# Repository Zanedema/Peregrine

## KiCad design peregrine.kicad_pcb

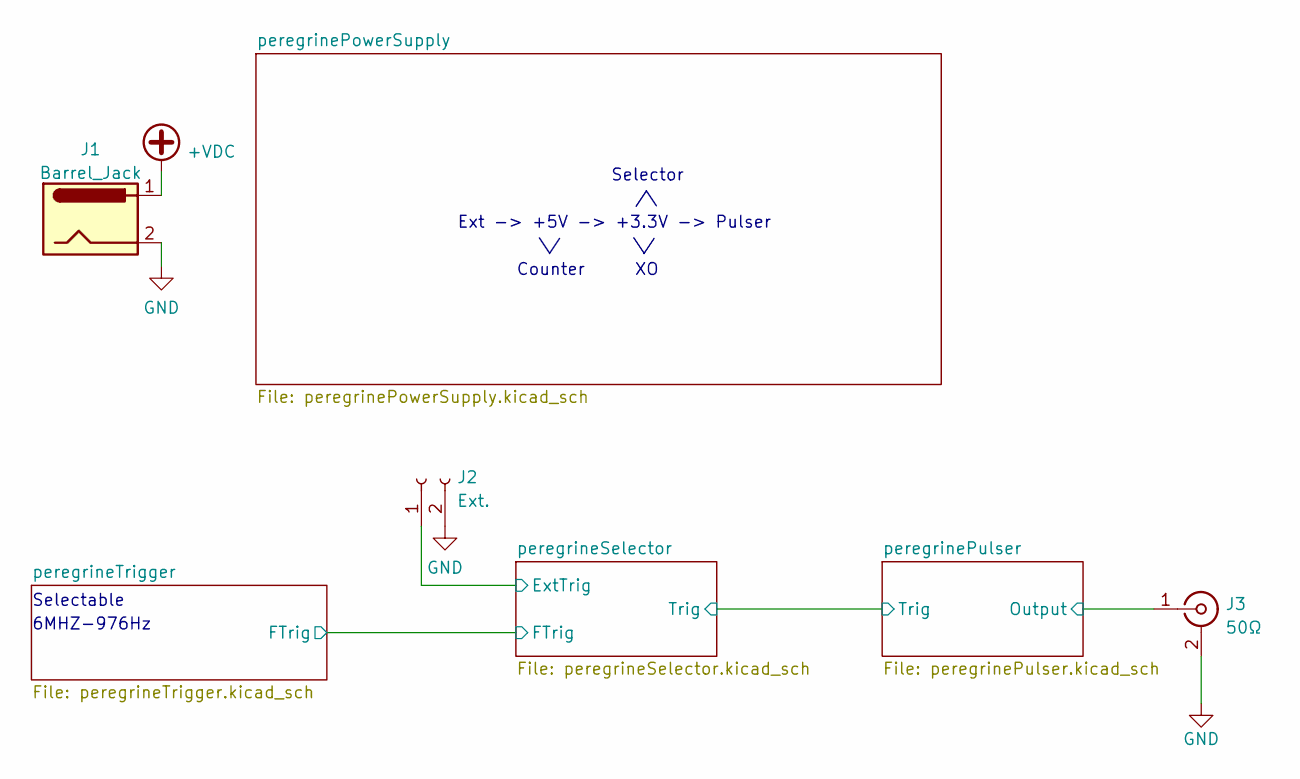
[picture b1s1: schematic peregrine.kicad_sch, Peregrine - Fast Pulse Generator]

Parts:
J1: Barrel_Jack; KLDX-0202-A
J2: Ext.; PinHeader_1x02_P2.54mm_Vertical
J3: 50Ω; LINX_CONSMA020.062-G

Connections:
+VDC: J1.1; also elsewhere on the board
/peregrinePulser/Output: J3.1 (In); also elsewhere on the board
/peregrineSelector/ExtTrig: J2.1; also elsewhere on the board
GND: J1.2, J2.2, J3.2 (Ext); also elsewhere on the board

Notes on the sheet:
Ext -> +5V -> +3.3V -> Pulser
Selectable
6MHZ-976Hz
Counter
Selector

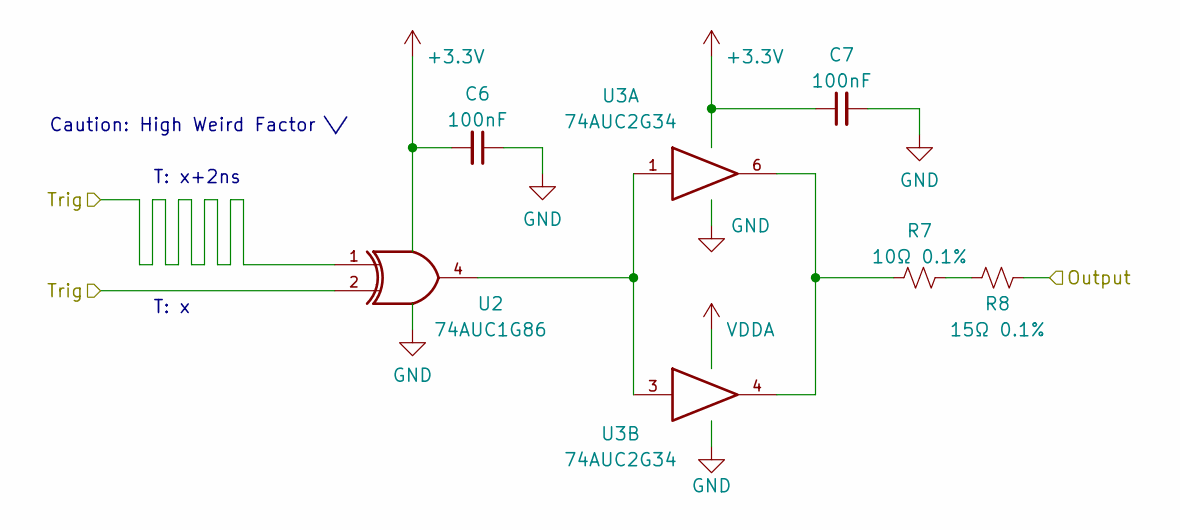
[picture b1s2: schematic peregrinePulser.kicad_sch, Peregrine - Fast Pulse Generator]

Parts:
C6, C7: 100nF; C_0603_1608Metric_Pad1.08x0.95mm_HandSolder
R7: 10Ω 0.1%; R_0603_1608Metric_Pad0.98x0.95mm_HandSolder
R8: 15Ω 0.1%; R_0603_1608Metric_Pad0.98x0.95mm_HandSolder
U2: 74AUC1G86; SOT-353_SC-70-5_Handsoldering
U3: 74AUC2G34; SOT-363_SC-70-6_Handsoldering

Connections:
/peregrinePulser/Output: R8.1; also elsewhere on the board
/peregrinePulser/Trig: U2.1, U2.2; also elsewhere on the board
GND: C6.1, C7.2, U2.3 (GND), U3.2 (GND); also elsewhere on the board
unnamed: R7.1, R8.2
unnamed: R7.2, U3.4, U3.6
unnamed: U2.4, U3.1, U3.3

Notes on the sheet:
T: x+2ns
Caution: High Weird Factor \/
T: x

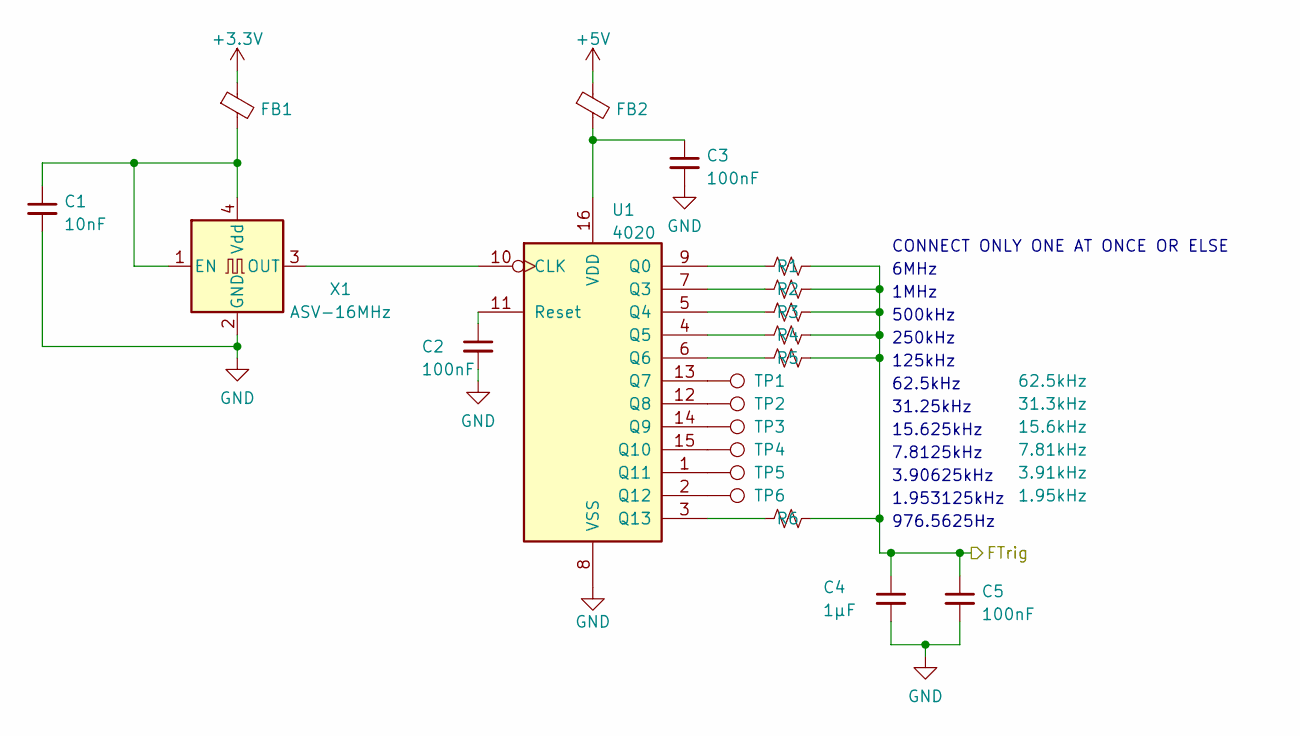
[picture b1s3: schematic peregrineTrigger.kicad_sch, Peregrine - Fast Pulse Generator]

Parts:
C1: 10nF; C_0603_1608Metric_Pad1.08x0.95mm_HandSolder
C2, C3, C5: 100nF; C_0603_1608Metric_Pad1.08x0.95mm_HandSolder
C4: 1μF; C_0603_1608Metric_Pad1.08x0.95mm_HandSolder
FB1, FB2: FerriteBead_Small; L_0603_1608Metric_Pad1.05x0.95mm_HandSolder
R1, R2, R3, R4, R5, R6: 0; R_0402_1005Metric_Pad0.72x0.64mm_HandSolder
TP1: 62.5kHz; TestPoint_Pad_D1.0mm
TP2: 31.3kHz; TestPoint_Pad_D1.0mm
TP3: 15.6kHz; TestPoint_Pad_D1.0mm
TP4: 7.81kHz; TestPoint_Pad_D1.0mm
TP5: 3.91kHz; TestPoint_Pad_D1.0mm
TP6: 1.95kHz; TestPoint_Pad_D1.0mm
U1: 4020; TSSOP-16_4.4x5mm_P0.65mm
X1: ASV-16MHz; Oscillator_SMD_Abracon_ASV-4Pin_7.0x5.1mm

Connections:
+5V: FB2.1; also elsewhere on the board
/peregrineSelector/FTrig: C4.1, C5.1, R1.1, R2.1, R3.1, R4.1, R5.1, R6.1; also elsewhere on the board
GND: C1.2, C2.2, C3.2, C4.2, C5.2, U1.8 (VSS), X1.2 (GND); also elsewhere on the board
unnamed: C1.1, FB1.2, X1.1 (EN), X1.4 (Vdd)
unnamed: C2.1, U1.11 (Reset)
unnamed: C3.1, FB2.2, U1.16 (VDD)
unnamed: R1.2, U1.9 (Q0)
unnamed: R2.2, U1.7 (Q3)
unnamed: R3.2, U1.5 (Q4)
unnamed: R4.2, U1.4 (Q5)
unnamed: R5.2, U1.6 (Q6)
unnamed: R6.2, U1.3 (Q13)
unnamed: TP1.1, U1.13 (Q7)
unnamed: TP2.1, U1.12 (Q8)
unnamed: TP3.1, U1.14 (Q9)
unnamed: TP4.1, U1.15 (Q10)
unnamed: TP5.1, U1.1 (Q11)
unnamed: TP6.1, U1.2 (Q12)
unnamed: U1.10 (CLK), X1.3 (OUT)

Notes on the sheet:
1.953125kHz
3.90625kHz
31.25kHz
500kHz
CONNECT ONLY ONE AT ONCE OR ELSE
250kHz
15.625kHz
976.5625Hz
125kHz
62.5kHz
7.8125kHz
6MHz
1MHz

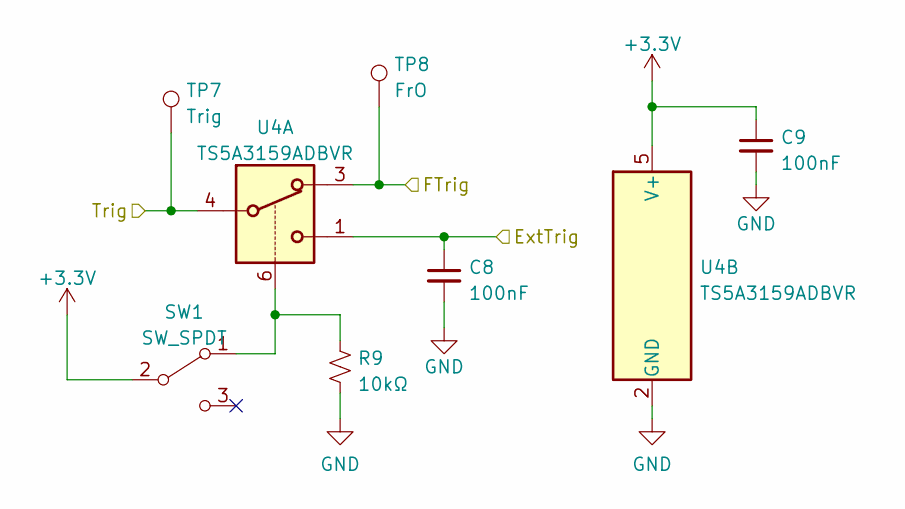
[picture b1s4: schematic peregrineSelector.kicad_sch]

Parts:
C8, C9: 100nF; C_0603_1608Metric_Pad1.08x0.95mm_HandSolder
R9: 10kΩ; R_0603_1608Metric_Pad0.98x0.95mm_HandSolder
SW1: SW_SPDT; JS102011SCQN
TP7: Trig; TestPoint_Pad_D1.0mm
TP8: FrO; TestPoint_Pad_D1.0mm
U4: TS5A3159ADBVR; SOT-23-6_Handsoldering

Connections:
/peregrinePulser/Trig: TP7.1, U4.4; also elsewhere on the board
/peregrineSelector/ExtTrig: C8.1, U4.1; also elsewhere on the board
/peregrineSelector/FTrig: TP8.1, U4.3; also elsewhere on the board
GND: C8.2, C9.2, R9.2, U4.2 (GND); also elsewhere on the board
unnamed: R9.1, SW1.1 (A), U4.6

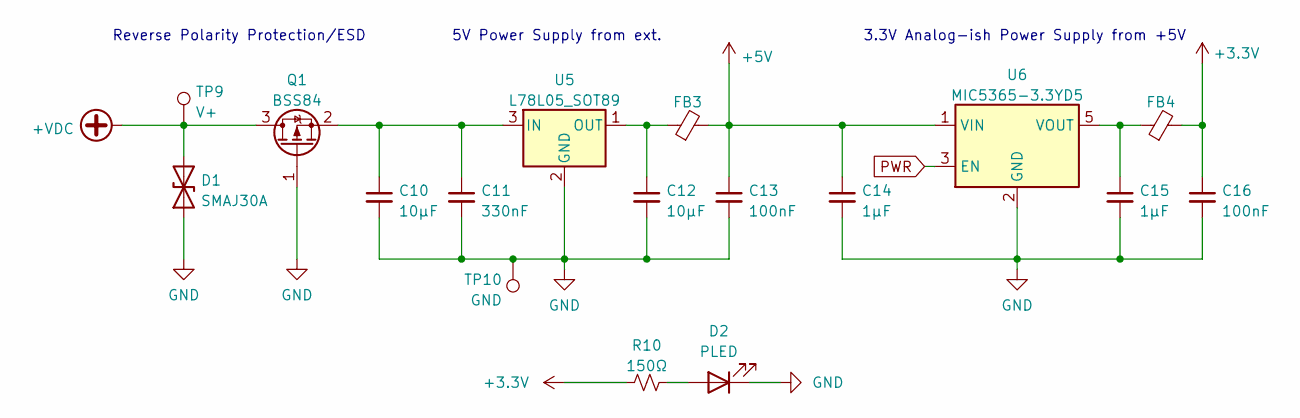
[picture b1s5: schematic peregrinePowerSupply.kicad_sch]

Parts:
C10, C12: 10μF; C_0805_2012Metric_Pad1.18x1.45mm_HandSolder
C11: 330nF; C_0805_2012Metric_Pad1.18x1.45mm_HandSolder
C13, C16: 100nF; C_0603_1608Metric_Pad1.08x0.95mm_HandSolder
C14, C15: 1μF; C_0603_1608Metric_Pad1.08x0.95mm_HandSolder
D1: SMAJ30A; D_SMA
D2: PLED; LED_0603_1608Metric_Pad1.05x0.95mm_HandSolder
FB3, FB4: FerriteBead_Small; L_0603_1608Metric_Pad1.05x0.95mm_HandSolder
Q1: BSS84; SOT-23
R10: 150Ω; R_0603_1608Metric_Pad0.98x0.95mm_HandSolder
TP9: V+; TestPoint_Pad_1.5x1.5mm
TP10: GND; TestPoint_Pad_1.5x1.5mm
U5: L78L05_SOT89; SOT-89-3
U6: MIC5365-3.3YD5; SOT-23-5_HandSoldering

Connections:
+5V: C13.1, C14.1, FB3.2, U6.1 (VIN); also elsewhere on the board
+VDC: D1.2 (A2), Q1.3 (D), TP9.1; also elsewhere on the board
GND: C10.2, C11.2, C12.2, C13.2, C14.2, C15.2, C16.2, D1.1 (A1), D2.1 (K), Q1.1 (G), TP10.1, U5.2 (GND), U6.2 (GND); also elsewhere on the board
unnamed: C10.1, C11.1, Q1.2 (S), U5.3 (IN)
unnamed: C12.1, FB3.1, U5.1 (OUT)
unnamed: C15.1, FB4.1, U6.5 (VOUT)
unnamed: D2.2 (A), R10.2
PWR: U6.3 (EN)

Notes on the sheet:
Reverse Polarity Protection/ESD
5V Power Supply from ext.
3.3V Analog-ish Power Supply from +5V

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
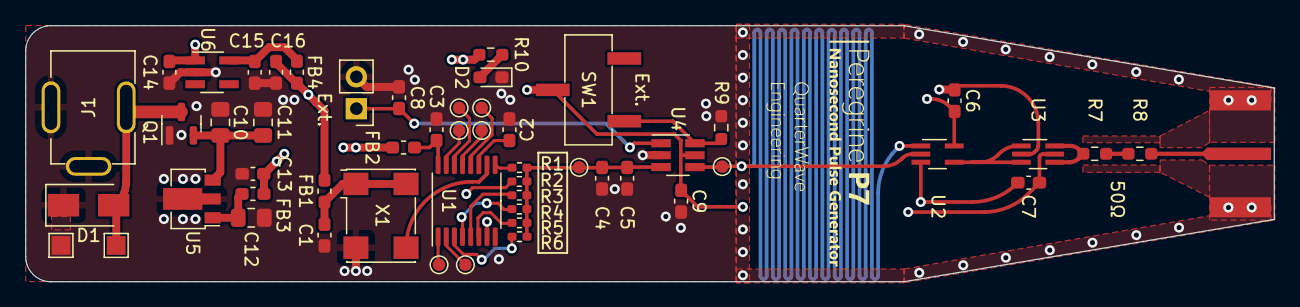
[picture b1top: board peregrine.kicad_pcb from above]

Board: 4 copper layers, 99.5 x 20.4 mm, 54 parts (0 on the bottom side), 32 nets.

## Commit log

2022-05-13 Initial schematic
2022-05-13 footprint changes
    get SMA, switches, and barrel tomorrow. am tired
2022-05-14 Delete #auto_saved_files#
    don't need this
2022-05-15 initial pcb pass
    ugh
2022-05-15 pcb improvements
    todo: sma
2022-05-29 I was doing this too
    hm
2022-05-30 ready for fab 1
    expensive and spooky. yay
2022-05-30 to make github be quiet
    ugh
2022-05-30 AGH
    I always forget that
2022-05-30 PCB ground plane cold feet
    leave the more uncomfy stuff for rev. 2
2022-06-09 this concerns me
    i feel like this is not going to be pretty. might need to simulate more
2022-06-09 no longer used
    bye
2022-06-20 redesign
    why yes i redesigned half of the entire board
2022-06-20 Production files
    i am Afraid

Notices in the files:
peregrine.kicad_pcb:
[Designed with <3 in San Diego - Licensed under MIT License]
parts and their libraries:
Copyright 2021 Accelerated Designs. All rights reserved.
